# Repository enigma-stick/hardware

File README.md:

# Enigma Stick

A compact USB-C hardware prototype built around an ESP32-C3-MINI-1 and an NXP SE051 secure element. This repository contains editable KiCad hardware sources, local libraries, preview images, a component list, and build notes. Firmware is developed separately and is not included here.

**Current revision: v1.1, prototype awaiting physical validation.** The base PCB is 34.4 × 20 mm, with the USB plug and antenna extending beyond its edges. ERC/DRC results and outstanding manufacturing checks are described in the [design review](docs/design-review.md). The SE051 rendering is an approximate package model.

## Open the design

1. Install KiCad 10 with its standard symbol, footprint, and 3D libraries. The latest render was made with KiCad 10.0.7.
2. Open [v1.1/enigma-stick-v1.1.kicad_pro](v1.1/enigma-stick-v1.1.kicad_pro) in KiCad's project manager.
3. Follow the [SE051 library setup instructions](docs/se051-library-setup.md) to download and register its standalone symbol and footprint locally; those files are excluded from Git. The design still contains its placed symbol and footprint, as explained in that guide.
4. Open the schematic or PCB from that project. Project-local libraries use relative paths. Some stock/Espressif 3D models require the corresponding installed libraries; missing optional models do not prevent editing the circuit.

Use v1.1 for current work. Konnect is optional for people using KiCad directly.

## Find your way around

| Location | Contents |
| --- | --- |
| [v1.1 project](v1.1/enigma-stick-v1.1.kicad_pro) | Current editable design |
| [Component list](v1.1/manufacturing/JLCPCB-BOM.csv) | Main assembly BOM |
| [Schematic preview](v1.1/reports/schematic.png) | Circuit overview without opening KiCad |
| [docs/build.md](docs/build.md) | Fabrication, assembly and prototype bring-up |
| [docs/design-review.md](docs/design-review.md) | Check results, warning dispositions and open checks |
| [SE051 library setup](docs/se051-library-setup.md) | Download and register the locally installed SE051 library |
| [v1.1/models/](v1.1/models/README.md) | 3D model sources and approximation limits |

## License and attribution

Original Enigma Stick hardware design and project-authored supporting material are licensed under [CERN-OHL-P-2.0](LICENSE). Copyright 2026 Enigma Stick contributors. Third-party libraries and models retain their own terms; see [THIRD_PARTY.md](THIRD_PARTY.md) and [LICENSES/](LICENSES/).

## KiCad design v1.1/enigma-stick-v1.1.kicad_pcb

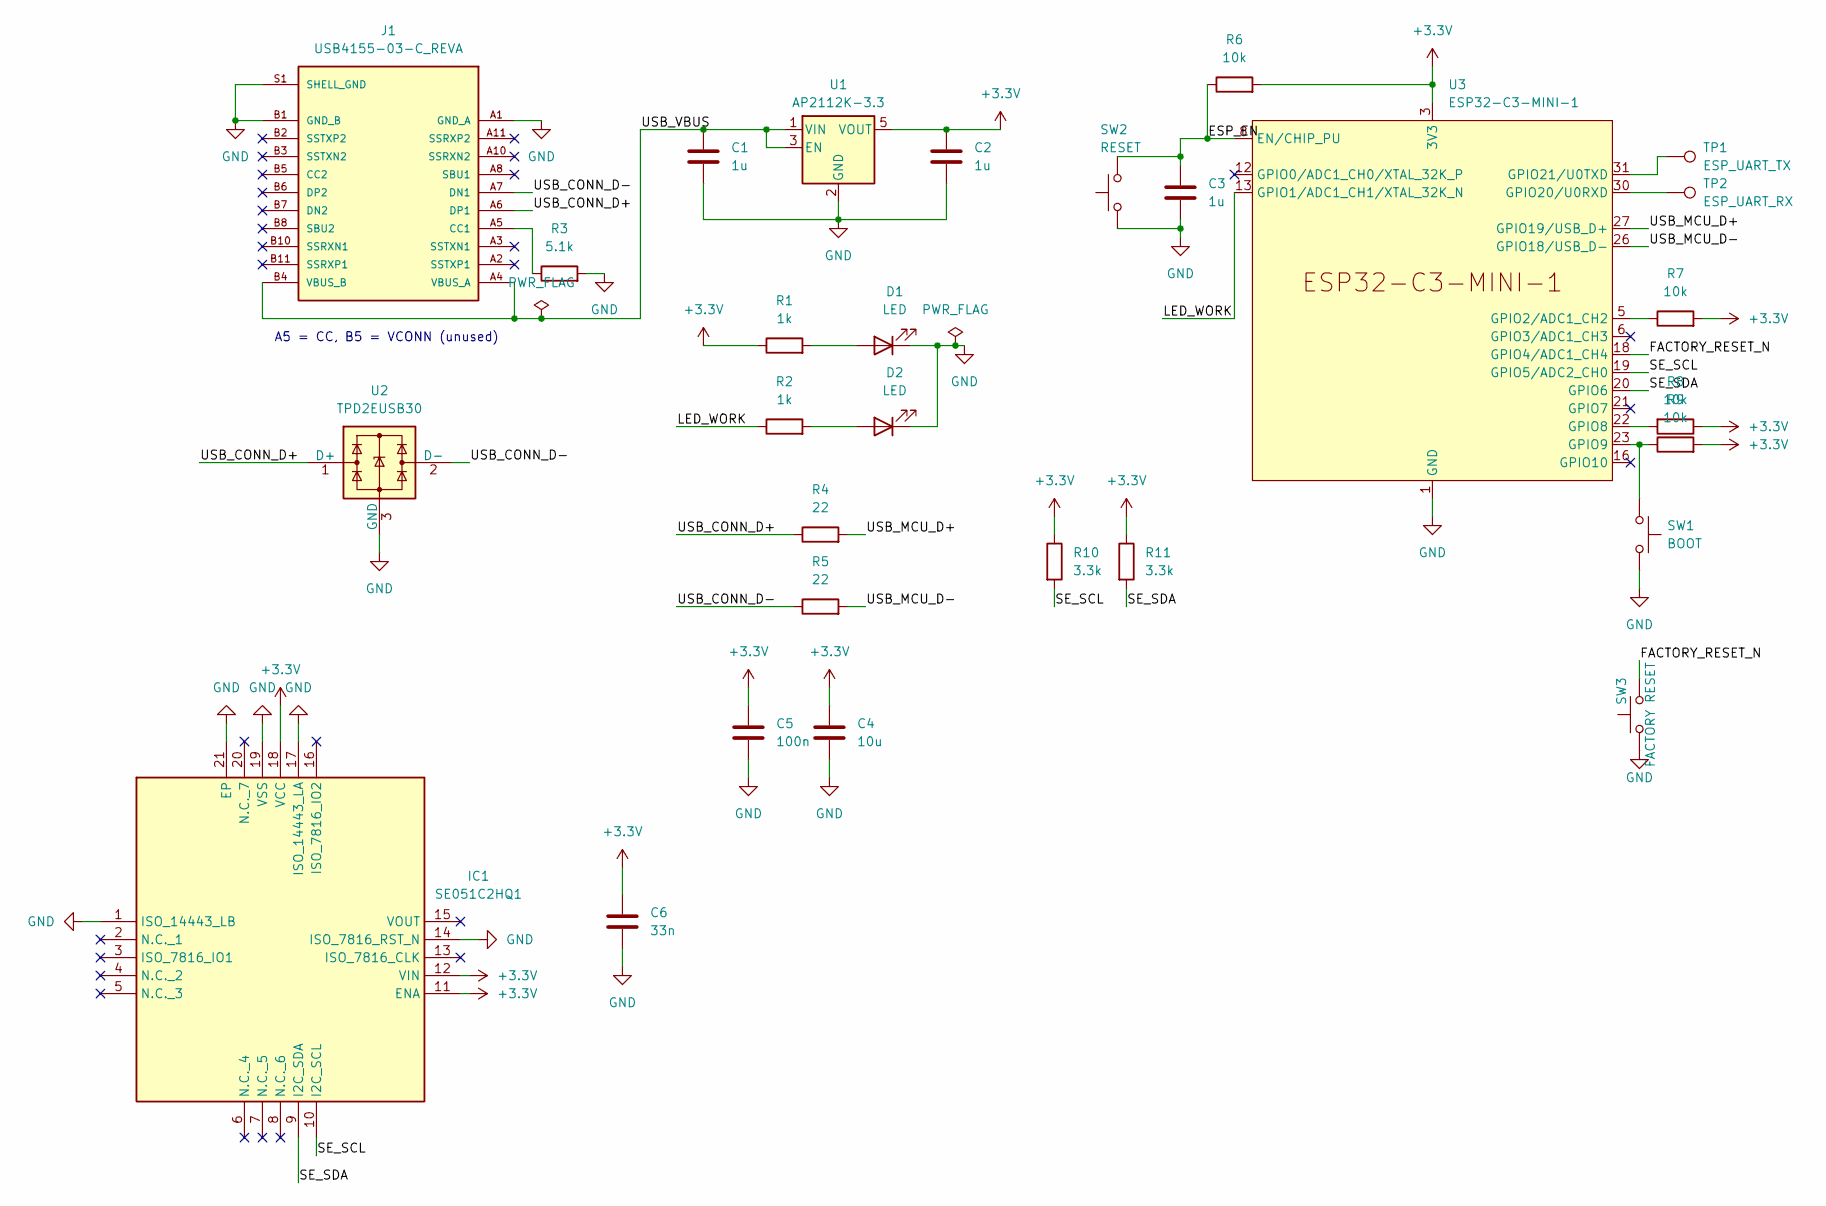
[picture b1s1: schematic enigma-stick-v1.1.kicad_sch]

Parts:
C1, C2, C3: 1u; C_0805_2012Metric; MPN CL21B105KOFNNNE; LCSC C24123
C4: 10u; C_0805_2012Metric; MPN CL21A106KAYNNNE; LCSC C15850
C5: 100n; C_0805_2012Metric; MPN CL21B104KBCNNNC; LCSC C1711
C6: 33n; C_0805_2012Metric; MPN 0805B333K500NT; LCSC C1739
D1, D2: LED; LED_0805_2012Metric; MPN LTST-C170KGKT; LCSC C98221
IC1: SE051C2HQ1; QFN40P300X300X33-21N-D; Manufacturer_Part_Number SE051C2HQ1; LCSC C5202100
J1: USB4155-03-C_REVA; GCT_USB4155-03-C_REVA; PARTREV A; LCSC C5183853
R1, R2: 1k; R_0805_2012Metric; MPN 0805W8F1001T5E; LCSC C17513
R3: 5.1k; R_0805_2012Metric; MPN 0805W8F5101T5E; LCSC C27834
R4, R5: 22; R_0805_2012Metric; MPN 0805W8F220JT5E; LCSC C17561
R6, R7, R8, R9: 10k; R_0805_2012Metric; MPN 0805W8F1002T5E; LCSC C17414
R10, R11: 3.3k; R_0805_2012Metric; MPN 0805W8F3301T5E; LCSC C26010
SW1: BOOT; SW_SPST_B3U-1000P; Manufacturer_Part_Number B3U-1000P; LCSC C231329
SW2: RESET; SW_SPST_B3U-1000P; Manufacturer_Part_Number B3U-1000P; LCSC C231329
SW3: FACTORY RESET; SW_SPST_B3U-1000P; MPN B3U-1000P; LCSC C231329
TP1: ESP_UART_TX; TestPoint_Pad_D1.0mm
TP2: ESP_UART_RX; TestPoint_Pad_D1.0mm
U1: AP2112K-3.3; SOT-23-5; MPN AP2112K-3.3TRG1; LCSC C51118
U2: TPD2EUSB30; Texas_DRT-3; MPN TPD2EUSB30DRTR; LCSC C97502
U3: ESP32-C3-MINI-1; MPN ESP32-C3-MINI-1-N4; LCSC C2838502

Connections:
+3.3V: C2.1, C4.1, C5.1, C6.1, IC1.11 (ENA), IC1.12 (VIN), IC1.18 (VCC), R1.1, R6.2, R7.2, R8.1, R9.2, R10.1, R11.1, U1.5 (VOUT), U3.3 (3V3)
/ESP_EN: C3.1, R6.1, SW2.2, U3.8 (EN/CHIP_PU)
/FACTORY_RESET_N: SW3.2, U3.18 (GPIO4/ADC1_CH4)
/LED_WORK: R2.1, U3.13 (GPIO1/ADC1_CH1/XTAL_32K_N)
/SE_SCL: IC1.10 (I2C_SCL), R10.2, U3.19 (GPIO5/ADC2_CH0)
/SE_SDA: IC1.9 (I2C_SDA), R11.2, U3.20 (GPIO6)
/USB_CONN_D+: J1.A6 (DP1), R4.1, U2.1 (D+)
/USB_CONN_D-: J1.A7 (DN1), R5.1, U2.2 (D-)
/USB_MCU_D+: R4.2, U3.27 (GPIO19/USB_D+)
/USB_MCU_D-: R5.2, U3.26 (GPIO18/USB_D-)
/USB_VBUS: C1.1, J1.A4 (VBUS_A), J1.A9 (VBUS_A), J1.B4 (VBUS_B), J1.B9 (VBUS_B), U1.1 (VIN), U1.3 (EN)
GND: C1.2, C2.2, C3.2, C4.2, C5.2, C6.2, D1.1 (K), D2.1 (K), IC1.1 (ISO_14443_LB), IC1.14 (ISO_7816_RST_N), IC1.17 (ISO_14443_LA), IC1.19 (VSS), IC1.21 (EP), J1.A1 (GND_A), J1.A12 (GND_A), J1.B1 (GND_B), J1.B12 (GND_B), J1.S1 (SHELL_GND), J1.S2 (SHELL_GND), R3.2, SW1.2, SW2.1, SW3.1, U1.2 (GND), U2.3 (GND), U3.1 (GND), U3.2 (GND), U3.11 (GND), U3.14 (GND), U3.36 (GND), U3.37 (GND), U3.38 (GND), U3.39 (GND), U3.40 (GND), U3.41 (GND), U3.42 (GND), U3.43 (GND), U3.44 (GND), U3.45 (GND), U3.46 (GND), U3.47 (GND), U3.48 (GND), U3.49 (GND), U3.50 (GND), U3.51 (GND), U3.52 (GND), U3.53 (GND)
unnamed: D1.2 (A), R1.2
unnamed: D2.2 (A), R2.2
unnamed: J1.A5 (CC1), R3.1
unnamed: R7.1, U3.5 (GPIO2/ADC1_CH2)
unnamed: R8.2, U3.22 (GPIO8)
unnamed: R9.1, SW1.1, U3.23 (GPIO9)
unnamed: TP2.1 (1_1), U3.30 (GPIO20/U0RXD)
unnamed: TP1.1 (1_1), U3.31 (GPIO21/U0TXD)

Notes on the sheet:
A5 = CC, B5 = VCONN (unused)

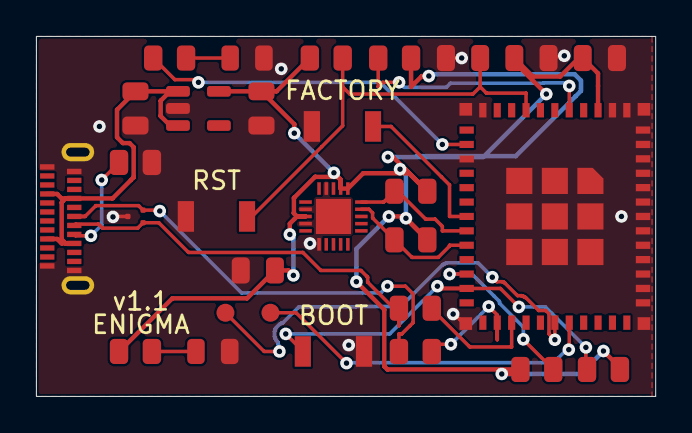
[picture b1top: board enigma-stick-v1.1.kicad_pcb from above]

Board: 2 copper layers, 34.4 x 20.0 mm, 29 parts (0 on the bottom side), 20 nets.

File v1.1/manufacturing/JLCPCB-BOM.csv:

Comment,Designator,Footprint,MPN,LCSC Part #
1u,"C1,C2,C3",Capacitor_SMD:C_0805_2012Metric,CL21B105KOFNNNE,C24123
10u,C4,Capacitor_SMD:C_0805_2012Metric,CL21A106KAYNNNE,C15850
100n,C5,Capacitor_SMD:C_0805_2012Metric,CL21B104KBCNNNC,C1711
33n,C6,Capacitor_SMD:C_0805_2012Metric,0805B333K500NT,C1739
LED,"D1,D2",LED_SMD:LED_0805_2012Metric,LTST-C170KGKT,C98221
SE051C2HQ1,IC1,Enigma_SE:QFN40P300X300X33-21N-D,SE051C2HQ1/Z01XDZ,C5202100
USB4155-03-C_REVA,J1,USB4155-03-C_REVA:GCT_USB4155-03-C_REVA,USB4155-03-C,C5183853
1k,"R1,R2",Resistor_SMD:R_0805_2012Metric,0805W8F1001T5E,C17513
5.1k,R3,Resistor_SMD:R_0805_2012Metric,0805W8F5101T5E,C27834
22,"R4,R5",Resistor_SMD:R_0805_2012Metric,0805W8F220JT5E,C17561
10k,"R6,R7,R8,R9",Resistor_SMD:R_0805_2012Metric,0805W8F1002T5E,C17414
3.3k,"R10,R11",Resistor_SMD:R_0805_2012Metric,0805W8F3301T5E,C26010
BOOT,SW1,Button_Switch_SMD:SW_SPST_B3U-1000P,B3U-1000P,C231329
RESET,SW2,Button_Switch_SMD:SW_SPST_B3U-1000P,B3U-1000P,C231329
FACTORY RESET,SW3,Button_Switch_SMD:SW_SPST_B3U-1000P,B3U-1000P,C231329
AP2112K-3.3,U1,Package_TO_SOT_SMD:SOT-23-5,AP2112K-3.3TRG1,C51118
TPD2EUSB30,U2,Package_TO_SOT_SMD:Texas_DRT-3,TPD2EUSB30DRTR,C97502
ESP32-C3-MINI-1,U3,PCM_Espressif:ESP32-C3-MINI-1,ESP32-C3-MINI-1-N4,C2838502
